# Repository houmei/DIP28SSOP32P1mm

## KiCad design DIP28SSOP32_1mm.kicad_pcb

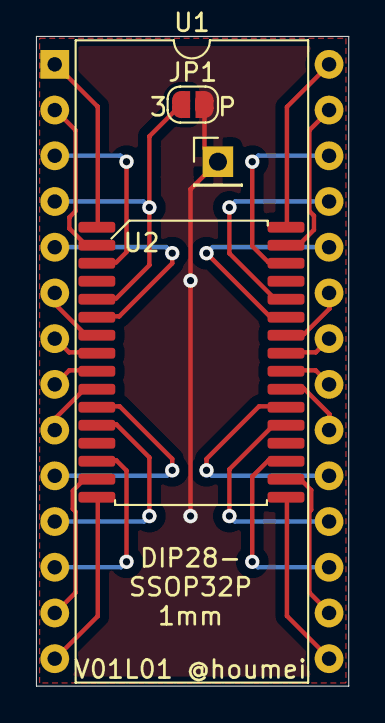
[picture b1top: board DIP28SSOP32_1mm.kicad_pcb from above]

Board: 2 copper layers, 17.3 x 36.1 mm, 4 parts (0 on the bottom side), 29 nets.

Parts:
J2: Conn_01x01_Male; PinHeader_1x01_P2.54mm_Vertical
JP1: SolderJumper_2_Open; SolderJumper-2_P1.3mm_Open_RoundedPad1.0x1.5mm
U1: 8251A; DIP-28_W15.24mm
U2: 8251A-SSOP; SSOP-32_7.9x15.95mm_P1mm

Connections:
CD: U1.12, U2.14
CLK: U1.20, U2.23
D0: U1.27, U2.31
D1: U1.28, U2.32
D2: U1.1, U2.1
D3: U1.2, U2.2
D4: U1.5, U2.6
D5: U1.6, U2.7
D6: U1.7, U2.8
D7: U1.8, U2.9
GND: JP1.1, U1.4, U2.5
PLANE: J2.1, JP1.2
RESET: U1.21, U2.24
RxC: U1.25, U2.28
RxD: U1.3, U2.3
RxRDY: U1.14, U2.16
SYNDET: U1.16, U2.18
TxC: U1.9, U2.10
TxD: U1.19, U2.22
TxEMPTY: U1.18, U2.21
TxRDY: U1.15, U2.17
Vcc: U1.26, U2.30
~CS: U1.11, U2.12
~CTS: U1.17, U2.19
~DSR: U1.22, U2.25
~DTR: U1.24, U2.27
~RD: U1.13, U2.15
~RTS: U1.23, U2.26
~WR: U1.10, U2.11
